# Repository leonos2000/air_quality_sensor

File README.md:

# Air Quality Sensor

## Overview

This is air quality sensor that can measure PM1.0, PM2.5, PM10, tVOC and eCO2, but also temperature and humidity.

This is second version of my project witch has some improvements for example separators in 3d printed casing that prevent heating DHT22 sensor from nodeMCU.

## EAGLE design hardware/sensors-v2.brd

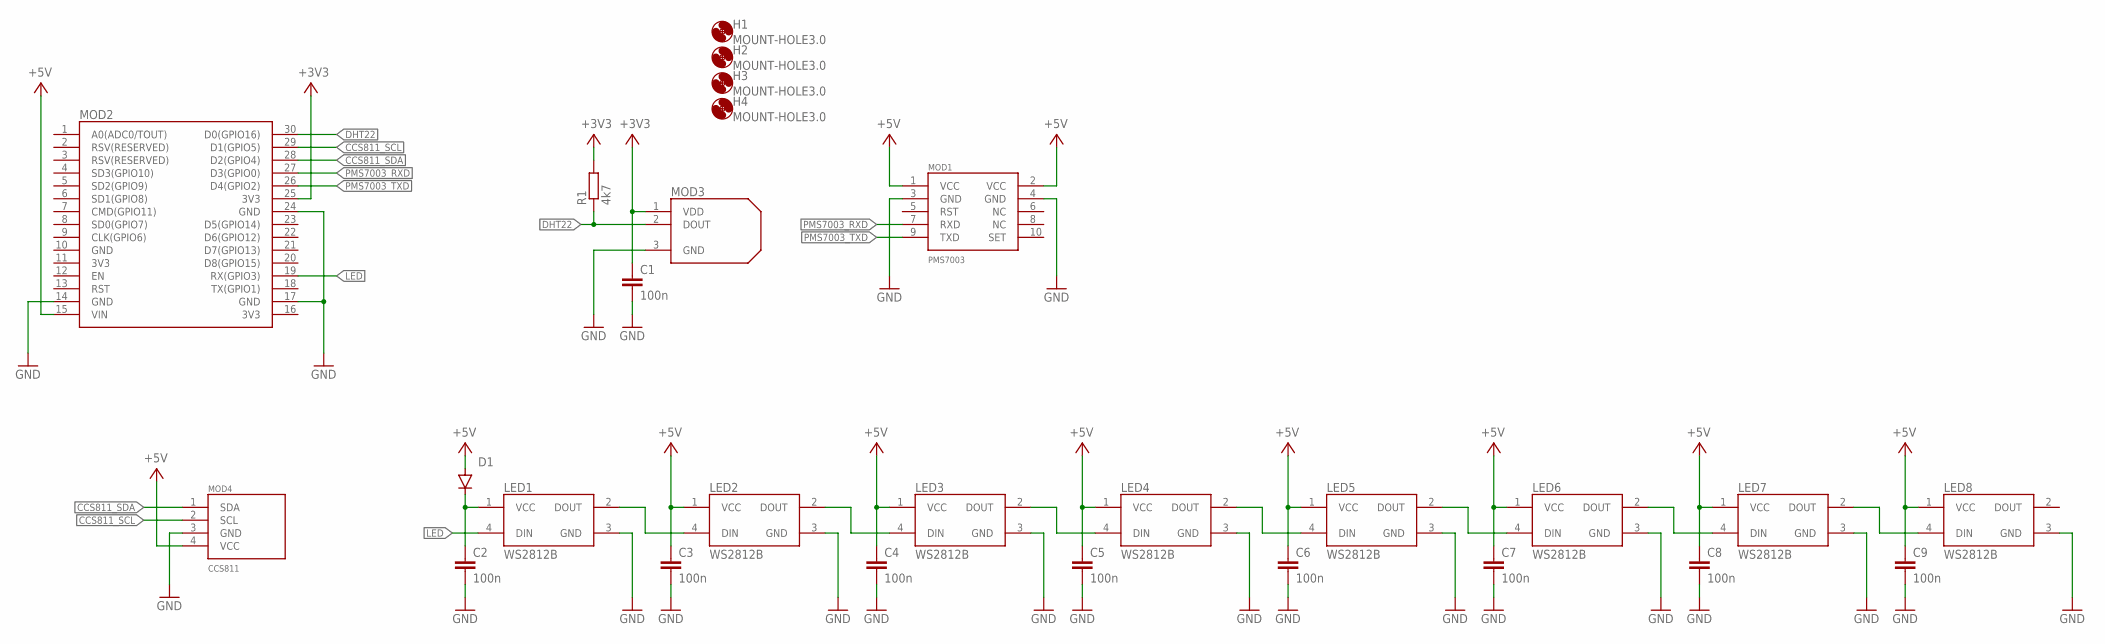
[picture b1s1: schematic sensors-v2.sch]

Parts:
C1, C2, C3, C4, C5, C6, C7, C8, C9: 100n; C0603
D1: DIODE-MINIMELF; MINIMELF
H1, H2, H3, H4: MOUNT-HOLE3.0; 3,0
LED1, LED2, LED3, LED4, LED5, LED6, LED7, LED8: WS2812B
MOD1: PMS7003
MOD2: NODEMCU; NODEMCU-WITHOUT-HOLES
MOD3: DHT22; DHT22_STRAIGHT-3PIN
MOD4: CCS811; HDRRAR4W64P254_1X4_1016X736X254B
R1: 4k7; M0805

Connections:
+3V3: C1.1, MOD2.25 (3V3), MOD3.1 (VDD), R1.2
+5V: C3.1, C4.1, C5.1, C6.1, C7.1, C8.1, C9.1, D1.A, LED2.1 (VCC), LED3.1 (VCC), LED4.1 (VCC), LED5.1 (VCC), LED6.1 (VCC), LED7.1 (VCC), LED8.1 (VCC), MOD1.1 (VCC), MOD1.2 (VCC), MOD2.15 (VIN), MOD4.4 (VCC)
CCS811_SCL: MOD2.29 (D1(GPIO5)), MOD4.2 (SCL)
CCS811_SDA: MOD2.28 (D2(GPIO4)), MOD4.1 (SDA)
DHT22: MOD2.30 (D0(GPIO16)), MOD3.2 (DOUT), R1.1
GND: C1.2, C2.2, C3.2, C4.2, C5.2, C6.2, C7.2, C8.2, C9.2, LED1.3 (GND), LED2.3 (GND), LED3.3 (GND), LED4.3 (GND), LED5.3 (GND), LED6.3 (GND), LED7.3 (GND), LED8.3 (GND), MOD1.3 (GND), MOD1.4 (GND), MOD2.14 (GND), MOD2.17 (GND), MOD2.24 (GND), MOD3.3 (GND), MOD4.3 (GND)
LED: LED1.4 (DIN), MOD2.19 (RX(GPIO3))
unnamed: C2.1, D1.C, LED1.1 (VCC)
unnamed: LED2.2 (DOUT), LED3.4 (DIN)
unnamed: LED3.2 (DOUT), LED4.4 (DIN)
unnamed: LED1.2 (DOUT), LED2.4 (DIN)
unnamed: LED4.2 (DOUT), LED5.4 (DIN)
unnamed: LED5.2 (DOUT), LED6.4 (DIN)
unnamed: LED6.2 (DOUT), LED7.4 (DIN)
unnamed: LED7.2 (DOUT), LED8.4 (DIN)
PMS7003_RXD: MOD1.7 (RXD), MOD2.27 (D3(GPIO0))
PMS7003_TXD: MOD1.9 (TXD), MOD2.26 (D4(GPIO2))

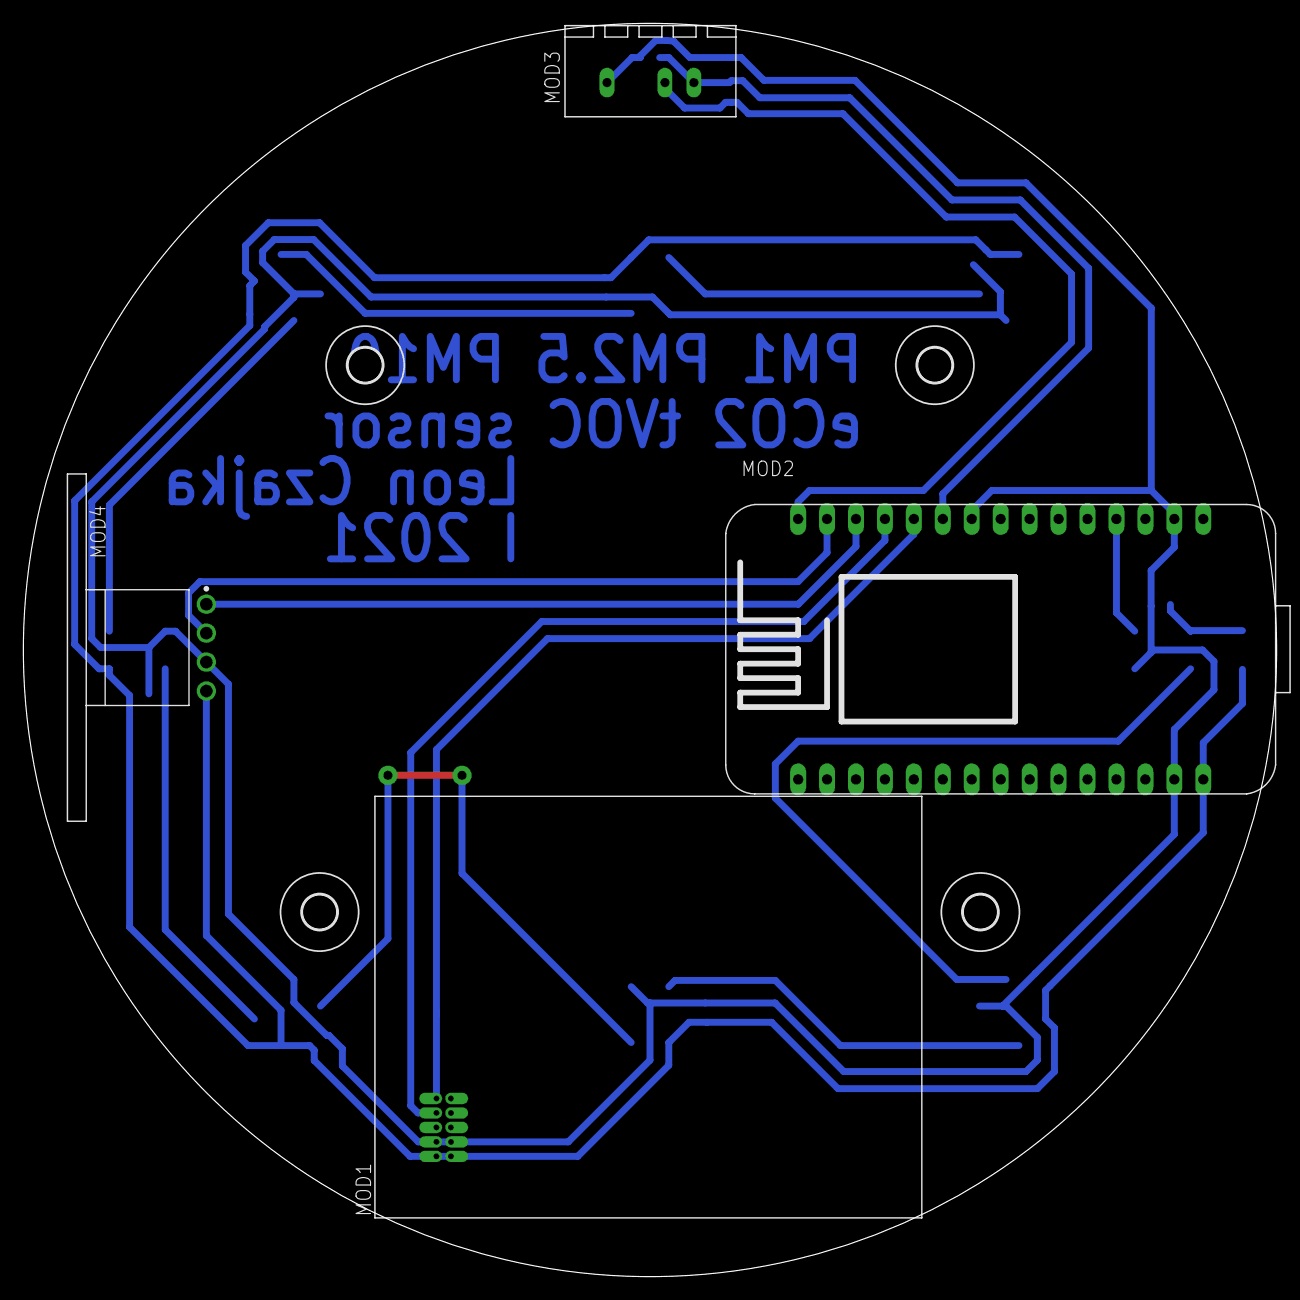
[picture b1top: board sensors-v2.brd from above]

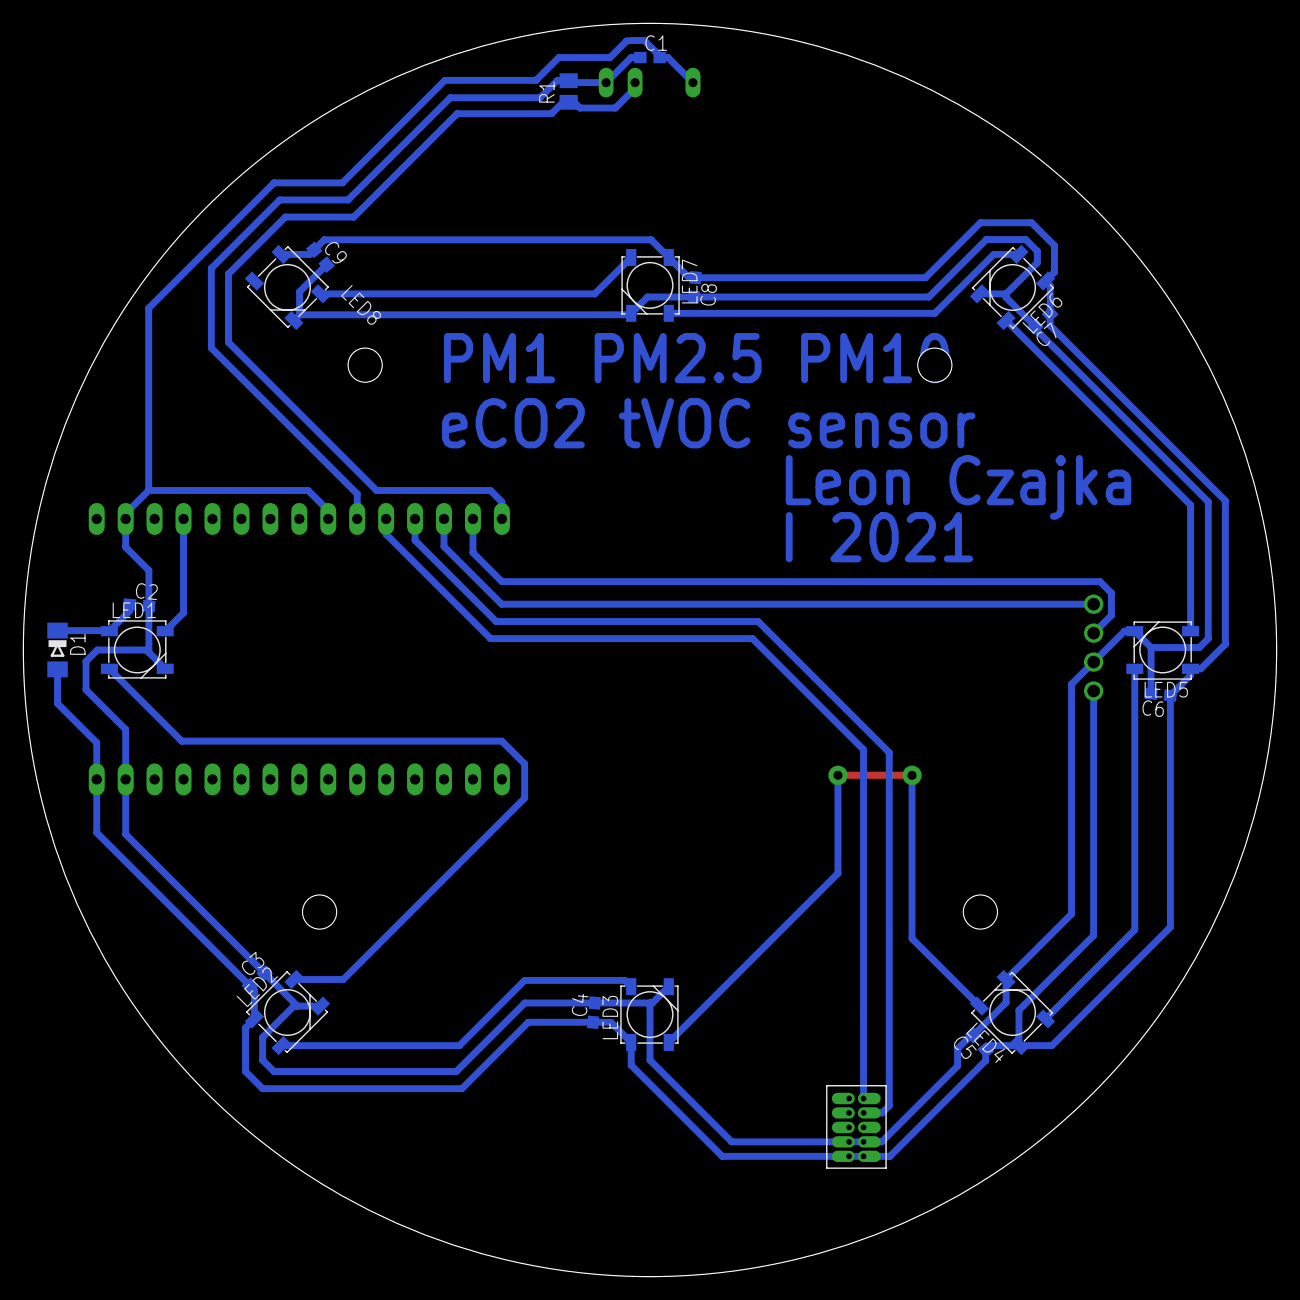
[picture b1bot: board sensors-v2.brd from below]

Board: 2 copper layers, 110.0 x 110.0 mm, 27 parts (19 on the bottom side), 17 nets.

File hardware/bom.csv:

Part;Value;Device;Package
C1;100n;C-EUC0603;C0603
C2;100n;C-EUC0603;C0603
C3;100n;C-EUC0603;C0603
C4;100n;C-EUC0603;C0603
C5;100n;C-EUC0603;C0603
C6;100n;C-EUC0603;C0603
C7;100n;C-EUC0603;C0603
C8;100n;C-EUC0603;C0603
C9;100n;C-EUC0603;C0603
D1;1N4148;DIODE-MINIMELF;MINIMELF
LED1;WS2812B;WS2812B;WS2812B
LED2;WS2812B;WS2812B;WS2812B
LED3;WS2812B;WS2812B;WS2812B
LED4;WS2812B;WS2812B;WS2812B
LED5;WS2812B;WS2812B;WS2812B
LED6;WS2812B;WS2812B;WS2812B
LED7;WS2812B;WS2812B;WS2812B
LED8;WS2812B;WS2812B;WS2812B
MOD1;PMS7003;PMS7003;PMS7003
MOD2;NODEMCU;NODEMCUWITHOUT-HOLES;NODEMCU-WITHOUT-HOLES
MOD3;DHT22;DHT22-3PIN;DHT22_STRAIGHT-3PIN
MOD4;CCS811;CCS811_ANGLE;HDRRAR4W64P254_1X4_1016X736X254B
R1;4k7;R-EU_M0805;M0805
SPACER1;M3x10mm;;
SPACER2;M3x10mm;;
SPACER3;M3x10mm;;
SPACER4;M3x10mm;;
BOLT1;M3x10mm Cone;;
BOLT2;M3x10mm Cone;;
BOLT3;M3x10mm Cone;;
BOLT4;M3x10mm Cone;;

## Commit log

2021-07-19 added files
2021-07-19 new image
